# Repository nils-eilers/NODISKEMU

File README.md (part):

NODISKEMU
=========

SD/MMC to IEEE-488 interface/controller
---------------------------------------

Introduction
------------

NODISKEMU is firmware, used in hardware designs like petSD, petSD+ or
Dave Curran's pet microSD that allows the IEEE-488 bus to access
SD cards  - think of it as a CBM 2031 with a modern storage medium instead
of disks. The project was inspired by (and uses a few bits of code from)
MMC2IEC[1] by Lars Pontoppidan and once ran on the same hardware before it
grew too big for the ATmega32 used there.

Currently, the firmware provide good DOS and file-level compatibility with CBM
drives, but much work remains.  Unless specifically noted, anything that tries
to execute code on the device will not work, this includes every software
fastloader.

NODISKEMU is a fork of sd2iec[2] by Ingo Korb (et al.) and is not intended to
be used on devices equipped with a Commodore serial bus, such as MMC2IEC,
SD2IEC or uIEC. Though most code still persists, compilation for these targets
may break at any time or is already broken. You better keep using sd2iec
for those.

1. http://pontoppidan.info/lars/index.php?proj=mmc2iec
2. http://sd2iec.de

Are you kidding me?
-------------------

This actually **IS** a disk emulator, isn't?

NODISKEMU does not emulate any particular vintage Commodore disk drive.
It neither emulates a 6502 CPU nor does it run any Commodore DOS.
It's just a storage solution that is capable to interact on low level
functions such as OPEN or TALK and interprets commands sent to channel 15
in a way similar to other drives.

The deeper meaning of this name is to clarify that there actually are
and ever will be some differences compared to real floppy drives.

Supported cards
---------------
MMC, SD and SHDC cards (resp. microSD/microSDHC cards) are supported,
formatted with either FAT16 or FAT32.

SDXC, microSDXC or ex-FAT won't work.

If you card refuses to work, try to format it with SD Formatter 4.0,
freely available for Windows and Mac from
https://www.sdcard.org/downloads/formatter_4/

Compatibility (IEEE-488)
------------------------

### Known good ###

Devices with IEEE-488 bus are compatible with any CBM/PET computer
equipped with either BASIC 2, BASIC 4 or BSOS.

The CBM-II series are fully supported, however you might want to
upgrade to a recent KERNAL because the older ones contain a couple
of bugs. The PROXA 7000 extension is fully supported.

OS-9 on the SuperPET is reported to boot from the FAT filesystem, but not
from disk images.

### Issues ###

The original PET equipped with BASIC 1 is not compatible because of its
hopelessly broken IEEE routines.

There are known issues with printer interfaces by Ultra Eletronic or
several clones of them, including mine.

### Untested ###

Tests are still missing for the Z-RAM card (a Z80 CP/M board)
and the softbox by Small Systems Engineering, Ltd. which is a Z80 CP/M
computer attached to the IEEE-488 bus.

Directories
-----------

petSD's default unit number became 11 in order to avoid any conflicts
with CBM 8296 built-in drives which usually are set to 8. You may even
use a further disk drive as unit 9 without any conflicts to petSD's 11.

Displaying directories works as usual, either the BASIC 2 way with

```
LOAD"$",11
LIST
```

or `CATALOG` for BASIC 4. You can abbreviate to `cA` and specify the
unit address:

```
cAu11
```

There are however some more advanced features:

### Directory filters ###

To show only directories, both =B (CMD-compatible) and =D can be used.
On a real Commodore drive D matches everything.
To include hidden files in the directory, use *=H - on a 1541 this doesn't
do anything. NODISKEMU marks hidden files with an H after the lock mark,
i.e. "PRG<H" or "PRG H".

CMD-style "short" and "long" directory listings with timestamps are supported
("$=T"), including timestamp filters. Please read a CMD manual for a complete
description of the syntax, two basic examples are provided here:

Short format:
```
LOAD"$=T",11
LIST
```

Long format:
```
LOAD"$=T:*=L",11
LIST
```

### Partition directory ###

The CMD-style partition directory ($=P) is supported, including filters
($=P:S*). All partitions are listed with type "FAT", although this could
change to "NAT" later for compatibility.

### Printing the directory ###

This example assumes a printer attached as unit 4:

```
LOAD "$",11
OPEN 4,4:CMD 4
LIST
PRINT#4:CLOSE 4
```

Sending Disk Commands
---------------------

BASIC 2 has only a very limited number of disk commands built-in:
`LOAD, SAVE, VERIFY, OPEN, CLOSE, GET#, INPUT#` and `PRINT#`.
For anything else beyond basic loading and saving programs and displaying
the directory, you have to send disk commands to the command channel 15
of the drive.

This can be done in two ways, either by appending the command to the OPEN
command or by sending it separately with the PRINT# command. An an example:

```
OPEN1,11,15,"CD:DIRNAME":CLOSE1
```
This opens the logical channel 1 on device 8 and sends the string `CD:DIRNAME`
to the command channel 15.

BASIC 4 adds some more advanced commands such as `CATALOG`. BASIC parses the
given parameters and builds a command string which is then sent to the command
channel 15, so it's just a more convenient wrapper for sending disk commands
but it doesn't add any DOS functions, they're still all processed inside the
disk drive.

However, even though BASIC 4 knows some more disk commands, they're kind of
limited in their usage. The most advanced and most comfortable way is to use a
so called DOS wedge. It cannot be used inside programs, only in direct mode.

Preceed any disk command with a `@` or a `>`, everything after that will be
sent to the command channel 15, e.g.:

```
@CD:DIRNAME
```

A loadable DOS wedge (as a terminate and stay resident program) is available
from http://petsd.net/wedge.php for CBM/PET computers with BASIC 2 and BASIC 4
and from http://cbm2wedge.sourceforge.net for the CBM-II series.

Better yet, get an updated editor ROM with built-in wedge[1] or upgrade your
CBM 8296 to BSOS[2] to have the wedge available right from the start after
power-on.

1. http://www.6502.org/users/sjgray/projects/editrom
2. https://github.com/Edilbert/BSOS

Retrieving the Disk Status
--------------------------

If an error occurs, a red LED of the drive flashes to indicate an error. To
get the error message, you have to retrieve the disk status by reading from
channel 15.

Unfortunately, BASIC 2 has no built-in command for this purpose, so it's
rather cumbersome:

```
10 OPEN1,11,15
20 INPUT#1,E,E$,T,S
30 PRINT E;E$;T;S
40 CLOSE1
```

`INPUT` doesn't work in direct mode, so you'll really have to write a short
program to retrieve and display the disk status.

BASIC 4 does it better, it includes the pseudo variables `ds` and `ds$` which
it updates after disk operations from status channel 15. However, it misses
some changes occasionally so if you depend on really getting the current disk
status you're stuck with the old-fashioned way.

Again, the most comfortable way is to use a DOS wedge. Just hit `@` followed
by RETURN and you'll get always the current disk status.

Long File Names
---------------
Long file names (i.e names not within the 8.3 limits) are supported on
FAT, but for compatibility reasons the 8.3 name is used if the long
name exceeds 16 characters. If you use anything but ASCII characters
on the PC or their PETSCII equivalents on the Commodore you may
get strange characters on the other system because the LFN use
Unicode characters on disk, but NODISKEMU parses only the low byte
of each character in the name.

Valid FAT Filenames
-------------------
Valid characters for filenames on the FAT filesystem have an ASCII code
greater or equal 32 (space) and less or equal 126 ('~'). In general,
no control codes are allowed, only 7 bit ASCII characters minus some
special characters. These forbidden characters are:

        " * , / \ : = ? @

Furthermore, neither space nor the full stop ('.') are not allowed as first
or last character of a filename. If a filename contains any illegal
characters, the creation of X00 files is forced even if XE mode 0 is set.

Changing the Device Address
---------------------------
After power on, the device address gets restored from the EEPROM. If the
device has jumpers or switches to set the address, it will take this
setting if a change is detected compared to the last setting during power-on.

There are up to three ways to change the device address:

1. U0 command (see there)
2. Hardware (jumper or switches)
3. LCD menu system
4. PETSD.CFG, see "Multiple drives" below

Hardware jumpers are only read after power-on, a reset or power
cycle is required to apply any changes.

If there are conflicting situations (e.g. hardware jumpers set to address 10
but address 9 stored in EEPROM), the last change or command sets the address.

EEPROM file system
------------------
**WARNING**: The EEPROM file system is a newly-implemented file system
that may still contain bugs. Do not store data on it that you cannot
afford to lose. Always make sure that you have a backup. Also, the
format may change in later releases, so please expect that the
partition may need to be erased in the future.

Devices running NODISKEMU always have an EEPROM to store the system
configuration, but on some devices this EEPROM is much larger than
required. To utilize the empty space on these devices (currently any
microcontroller with at least 128K of flash), a special EEPROM file
system has been implemented. This can for example be used to store a
small file browser or fast loader so it can be used independent of the
storage medium that is currently inserted.

The EEPROM file system will always register itself on the last
partition number (see "Partitions" below). You can check the list of
partitions ("$=P") to find the current partition number of the EEPROM
file system or use the alias function (see below) to access it.

To simplify calculations, block numbers on the EEPROMFS are calculated
using 256 bytes per block instead of the usual 254 bytes as used by
Commodore drives. Internally, the allocation is even more fine-grained
(using 64 byte sectors), which means that the number of free blocks
shown on an empty file system may be less than the sum of the number
of blocks of all files on a full file system.

The EEPROM file system does not support subdirectories. It can be
formatted using the N: command as usual, but the disk name and ID are
ignored. The capacity of the EEPROM file system varies between
devices: On AVR devices it is 3.25 KBytes and at most 8 files can be
stored on it. On a2iec, the file system can hold 7 KBytes and at most
16 files can be stored on it. The actual number of files that can be
stored depends on the length of the files, longer files need more than
one directory entry.

Partitions
----------

NODISKEMU features a multi-partition support similar to that of the CMD
drives. The partitions (which may be on separate drives for some hardware
configurations) are accessed using the drive number of the commands
sent from the computer and are numbered starting with 1. Partition 0
is a special case: Because most software doesn't support drive numbers
or always sends drive number 0, this partition points to the currently
selected partition. By default, accesses to partition 0 will access
partition 1, this can be changed by sending "CP<num>" over the command
channel with <num> being an ASCII number from 1 to 255. "C<Shift-P"
(0x42 0xd0) works the same, but expects a binary partition number as the
third character of the command.

To allow a "stable" access to the EEPROM file system no matter how
many partitions are currently available, a special character has been
introduced that will always access the EEPROM file system (if
available). When NODISKEMU sees a "!" character where it expects a
partition number and the "!" character is directly followed by a colon
(i.e. "!:"), it will access the EEPROMFS if available. Direct access
using the assigned partition number is of course still
available. Additionally "$!" will always load the directory of the
EEPROM file system partition (if available), similar to "$1" to "$9"
for partitions 1 to 9.

Multiple drives
---------------

With the build option `CONFIG_MULTIDRIVE` (enabled in `config-petSD+`),
a single device can answer on up to 4 bus addresses at the same time.
Each address is either a single drive or a dual drive with drive 0 and
drive 1, like a CBM 4040, 8050 or 8250, so there are up to 8 drives on
one SD card. Each drive points to a directory or to a disk image.

Without a configuration file nothing changes: the device behaves like a
single drive at the address stored in the EEPROM.

### PETSD.CFG ###

The drives are configured in the text file `PETSD.CFG` in the root
directory of the card, one line per drive:

```
# petSD+ drives
8:0  = /
8:1  = /GAMES
9:0  = /WORK
10:0 = /CBM8050/DISK1.D80
10:1 = /CBM8050/DISK2.D80
```

Rules:

- `address:drive = path`, blanks around `:` and `=` are allowed.
- Addresses 4 to 30, drive 0 or 1, at most 4 devices.
- A device needs drive 0, a line for drive 1 makes it a dual drive.
- The path starts at the root directory of the card and names a
  directory or a disk image. Upper and lower case do not matter, the
  maximum length is 112 characters.
- Names longer than 16 characters must be given as 8.3 short name,
  e.g. `/COLLEC~1`.
- Every line that does not match this pattern is a comment, usually
  starting with `#`. A comment after a path is not possible, it would
  become part of the path.
- If a drive is listed twice, the first line counts.
- The file is read at power-on and after every card change.

If the path of drive 1 does not exist, that drive reports
`74,DRIVE NOT READY`. If the path of drive 0 does not exist, the whole
device is missing. If no device is usable, the legacy single drive mode
with the EEPROM address is used.

### Drive numbers ###

With `PETSD.CFG` active, the number in front of the colon is the drive
number of the addressed device, not a partition number:

| Command                 | Meaning                                   |
|-------------------------|-------------------------------------------|
| `$`                     | directory of drive 0, then drive 1        |
| `$1`                    | directory of drive 1                      |
| `NAME` (read)           | search drive 0, then drive 1              |
| `NAME` (write)          | drive 0                                   |
| `0:NAME`, `1:NAME`      | drive 0 or drive 1                        |
| `1:NAME` (single drive) | `74,DRIVE NOT READY`                      |

This matches CBM DOS 2 dual drives, so the BASIC 4 commands work as
expected, e.g. `DIRECTORY D1,U8`, `DLOAD"NAME",D1,U8` or
`COPY D0,"OLD" TO D1,"NEW",U8`. The `C` command copies between drive 0
and drive 1 of the same device. Copying between two different bus
addresses needs the computer in between.

`CD`, `MD` and `RD` take the drive number right after the command:
`CD1:GAMES`, `CD1/GAMES/ACTION/`, `CD1//` (root of the card),
`CD1:_` (left arrow, one level up). Without a number they work on drive 0. Each drive
keeps its own current directory until the next card change or reset,
`PETSD.CFG` is not changed by `CD`.

### Changing addresses ###

- `U0>` and `M-W 119` change the address of the addressed device
  (both drives) until the next card change or reset. An address that is
  already taken or outside 4..30 is rejected with `30,SYNTAX ERROR`.
- `XW` stores the settings in the EEPROM as before. With `PETSD.CFG`
  active, it also writes the new address of the addressed device into
  the file. Only the address field of the lines of that device changes,
  everything else stays as it is. The file is written to `PETSD.TMP`
  first and then renamed.

### LCD menu ###

The main menu entry "Configure drives" replaces "Change device number".
It lists all drives and allows to add and remove devices and drive 1,
to change addresses and to choose a directory or disk image with a file
browser. "Save and exit" writes `PETSD.CFG` line by line, own comments
and blank lines are kept. Without `PETSD.CFG`, changing only the address
stores it in the EEPROM as before and no file is created.

With `PETSD.CFG` active, "Browse files" first asks for the drive to
browse.

### Card change ###

After a card change the configuration of the new card is read. A
command that is still pending for an address which does not exist on
the new card is discarded.

### Limitations ###

- Fast loaders (IEC only) are untested with more than one drive.
- The disk swap list (`XS`, `AUTOSWAP.LST`, swap buttons) is currently
  disabled in the firmware, with or without multiple drives.

x00 files
---------

P00/S00/U00/R00 files are transparently supported, that means they show
up in the directory listing with their internal file name instead of the
FAT file name. Renaming them only changes the internal name. The XE
command defines if x00 extensions are used when writing files, by
default NODISKEMU doesn't create x00 container files.

The creation of x00 files is forced if the filename contains
characters that would be illegal for FAT filenames. Spaces and dots are only
allowed within the filename but not as the first or last character.

Parsing of x00 files is always enabled even when writing them is not.

x00 files are recognized by checking both the extension of the file
(P/S/U/R with a two-digit suffix) and the header signature.

Disk Images
-----------

Disk images are recognized by their file extension (.D64, .D41, .D71, .D81,
.DNP) and their file size (must be one of 174848, 175531, 349696, 351062,
819200 or a multiple of 65536 for DNP). If the image has an error info block
appended it will be used to simulate read errors. Writing to a sector with
an error will always work, but it will not clear the indicated error.
D81 images with error info blocks are not supported.

Warning: There is at least one program out there (DirMaster v2.1/Style by
THE WIZ) which generates broken DNP files. The usual symptom is that
moving from a subdirectory that was created with this program back to
its parent directory using CD:_ (left arrow) sets the current directory
not to the parent directory, but to an incorrect sector instead. A
workaround for this problem in NODISKEMU would require an unreasonable
amount of system resources, so it is recommended to avoid creating
subdirectories with this version of DirMaster. It is possible to fix
this problem using a hex editor, but the exact process is beyond the scope
of this document.

REL files
---------

Partial REL file support is implemented. It should work fine for existing
files, but creating new files and/or adding records to existing files
may fail. REL files in disk images are not supported yet, only as files
on a FAT medium. When x00 support is disabled the first byte of a REL
file is assumed to be the record length.

Large buffers
-------------

To support commands which directly access the storage devices support
for larger buffers was added. A large buffer can be allocated by
opening a file named "##<d>" (exactly three characters" with <d> replaced
by a single digit specifying the number of 256-byte buffers to be
chained into one large buffer - e.g. "##2" for a 512 byte buffer,
"##4" for 1024 bytes etc. Unlike a standard buffer where the read/write
pointer is set to byte 1, a large buffer will start with the r/w pointer
pointing to byte 0 because that seems to be more sensible to the author.

If there aren't enough free buffers to support the size you requested
a 70,NO CHANNEL message is set in the error channel and no file is
opened. If the file name isn't exactly three bytes long a standard
buffer ("#") will be allocated instead for compatibility.

The B-P command supports a third parameter that holds the high byte
of the buffer position, For example, "B-P 9 4 1" positions to byte
260 (1\*256+4) of the buffer on secondary address 9.

LCD file browser
----------------

The LCD file browser uses available sector buffers to cache directory entries.
Even one free buffer is sufficient. If a directory is larger than the cache,
continue with NEXT or PREV to load the adjacent entries automatically.
"Reading..." indicates a reload; this rescans the directory to preserve
directory/image/name sorting on FAT. Disk images retain their native order.
Browser buffers are released before changing directories or mounting images.

Pressing SELECT on a regular file closes the entire menu and returns to the
status screen, on both FAT and inside disk images. Selecting a directory or
disk image enters it as usual. "Return to main menu" still returns to the
main menu.

Holding PREV or NEXT accelerates navigation after two and four seconds,
with repeat intervals of 150, 80 and 40 ms. Releasing the key or changing
direction restarts the initial speed.

Diagnostics
-----------

Because some SD slots seem to suffer from bad/unreliable card detect
switches a test mode for this has been implemented on the units that
have SD card support. To enable this test mode, hold down the PREV
button during power-up.

Devices with built-in LCD support (read: petSD+) will show their
diagnostics on the display if the menu system is enabled (see also:
XM command).

On petSD+, keep PREV held until the startup check has
completed to enter diagnostics, or NEXT to adjust LCD contrast.

The further notes apply only for devices without built-in LCD support
(read: old petSD and pet microSD):

The red (dirty) LED will reflect the card detect status - if the LED
is on the card detect switch is closed. Please note that this does not
indicate successful communication with the card but merely that the
mechanical switch in the SD card slot is closed.

On units with two NODISKEMU-controlled LEDs, the green (busy) LED will
indicate the state of the write protect switch - if the LED is lit,
the write protection is on. Due to the way the write protect notch
works on SD cards, the indication is only valid when the card is fully
inserted into the slot.

To exit from the diagnostic mode, power-cycle the device or push the
NEXT button once.

Other important notes
---------------------

- When you hold down the disk change (forward) button during power
  on the software will use default values instead of those stored
  in the EEPROM. (TODO: currently deactivated)
- File overwrite (@foo) is implemented by deleting the file first.
- File sizes in the directory are in blocks (of 254 bytes), but
  the blocks free message actually reports free clusters. It is
  a compromise of compatibility, accuracy and code size.
- If known, the low byte of the next line link pointer of the directory
  listing will be set to (filesize MOD 254)+2, so you can calculate the
  true size of the file if required. The 2 is added so it can never be
  mistaken for an end marker (0) or for the default value (1, used by at
  least the 1541 and 1571 disk drives).
- If your hardware supports more than one SD card, changing either one
  will reset the current partition to 1 and the current directory of
  all partitions to the root drive. Doing this just for the card that
  was changed would cause lots of problems if the number of partitions
  on the previous and the newly inserted cards are different.
- If you are the author of a program that needs to detect NODISKEMU for
  some reason, DO NOT use M-R for this purpose. Use the UI command
  instead and check the message you get for "nodiskemu" instead.

Reference of Disk Commands
--------------------------

### B-P ##

        B-P: channel position

Set the Buffer-Pointer associated with the given channel to a new value.
`B-P: 2 1` sets channel 2 pointer to the beginning of the data area in the
direct access buffer.

### B-R/B-W ###

        B-R: channel drive track sector
        B-W: channel drive track sector

Reads and writes blocks the clumsy way. Use U1/U2 instead for new programs.

### C ###

File copy command, should be CMD compatible. The syntax is

        C[partition][path]:targetname=[[partition][path]:]sourcename[,[[p][p]:]sourcename...]

You can use this command to copy multiple files into a single target
file in which case all source files will be appended into the target
file. Parsing restarts for every source file name which means that
every source name is assumed to be relative to the current directory.
You can use wildcards in the source names, but only the first
file matching will be copied.

Copying REL files should work, but isn't tested well. Mixing REL and
non-REL files in an append operation isn't supported.

### CD ###

CD (change directory) is used to select the current directory and to
mount or unmount disk images. Subdirectory access is compatible to the
syntax used by the CMD drives, although drive/partition numbers are
completely ignored.

Quick syntax overview:

Command        | Remarks
---------------|------------------------------------------------------------
`CD:_`         |changes into the parent dir (_ is the left arrow on the PET)
`CD_`          |ditto
`CD:foo`       |changes into foo
`CD/foo`       |ditto
`CD//foo`      |changes into \foo
`CD/foo/:bar`  |changes into foo\bar
`CD/foo/bar`   |ditto

You can use wildcards anywhere in the path. To change into an disk
image the image file must be the last component in the path, either
after a slash or a colon character.

To mount/unmount image files, change into them as if they were a directory
and use CD:_ (left arrow on the PET) to leave.
Please note that image files are detected by file extension and file size
and there is no reliable way to see if a file is a valid image file.

### CP, C\<Shift-P> ###

This changes the current partition, see "Partitions" below for details.

### D ###

Direct sector access, this is a command group introduced by NODISKEMU.
Some Commodore drives use D for disk duplication between two drives
in the same unit, an attempt to use that command with NODISKEMU should
result in an error message.

D has three subcommands: DI (Info), DR (Read) and DW (Write).
Each of those commands requires a buffer to be opened (similar
to U1/U2), but due to the larger sector size of the storage devices
used by NODISKEMU it needs to be a large buffer of size 2 (512 bytes)
or larger. The exception is the DI command with page set to 0,
its result will always fit into a standard 256 byte buffer.
If you try to use one of the commands with a buffer that is too
small a new error message is returned, "78,BUFFER TOO SMALL,00,00".

In the following paragraphs the secondary address that was used
to open the buffer is called "bufchan".

### DI ###
In BASIC notation the command format is

        "DI"+chr$(bufchan)+chr$(device)+chr$(page)

`device` is the number of the physical device to be queried,
`page` the information page to be retrieved. Currently the
only page implemented is page 0 which will return the
following data structure:

     1 byte : Number of valid bytes in this structure
              This includes this byte and is meant to provide
              backwards compatibility if this structure is extended
              at a later time. New fields will always be added to
              the end so old programs can still read the fields
              they know about.
     1 byte : Highest diskinfo page supported
              Always 0 for now, will increase if more information
              pages are added (planned: Complete ATA IDENTIFY
              output for IDE and CSD for SD)
     1 byte : Disk type
              This field identifies the device type, currently
              implemented values are:
                0  IDE
                2  SD
                3  (reserved)
     1 byte : Sector size divided by 256
              This field holds the sector size of the storage device
              divided by 256.
     4 bytes: Number of sectors on the device
              A little-endian (same byte order as the 6502) value
              of the number of sectors on the storage device.
              If there is ever a need to increase the reported
              capacity beyond 2TB (for 512 byte sectors) this
              field will return 0 and a 64-bit value will be added
              to this diskinfo page.

If you want to determine if there is a device that responds
to a given number, read info page 0 for it. If there is no
device present that corresponds to the number you will see
a DRIVE NOT READY error on the error channel and the
"number of valid bytes" entry in the structure will be 0.

Do not assume that device numbers are stable between releases
and do not assume that they are continuous either. To scan
for all present devices you should query at least 0-7 for now,
but this limit may increase in later releases.

### DR/DW ###

In BASIC notation the command format would be
```
      "DR"+chr$(bufchan)+chr$(device)
          +chr$(sector AND 255)
          +chr$((sector/256) AND 255)
          +chr$((sector/65536) AND 255)
          +chr$((sector/16777216) AND 255)
```
(or "DW" instead of "DR)

but this won't work on the C64 because AND does not accept
parameters larger than 32767. The principle should be clear
though, the last four bytes are a 32 bit sector number in
little-endian byte order.

DR reads the sector to the buffer, DW writes the contents
of the buffer to the sector. Both commands will update the
error channel if an error occurs, for DR the 20,READ ERROR
was chosen to represent read errors; for write problems
during DW it sets 25,WRITE ERROR for errors and 26,WRITE
PROTECT ON if the device is read-only.

### G-P ###

Get partition info, see CMD FD/HD manual for details. The reported
information is partially faked, feedback is welcome.

### MD ###

Makes (creates) a directory. MD uses a syntax similar to CD and
will create the directory listed after the colon (:) relative to
any directory listed before it.

`MD/foo/:bar` creates bar in foo

`MD//foo/:bar` creates bar in \foo

### M-R, M-W, M-E ###

When no file is set up using XR, M-R will check a small internal
table of common drive-detection addresses and return data that
forces most of the supported fast loaders into a compatible mode
(e.g. 1541 mode for Dreamload and ULoad Model 3, disabled
fastloader for Action Replay 6). If the address is not
recognized, more-or-less random data will be returned.

  Unfortunately GEOS reads rather large parts of the drive ROM
using M-R to detect the drive, which cannot be reasonably added
into the internal table. To enable the GEOS drive detection to
work properly with NODISKEMU and to allow switching between
1541/71/81 modes, file-based M-R emulation has been implemented.
If a file has been set up as M-R data source using the XR
command, its contents will be returned for M-R commands that try
to read an address in the range of $8000-$ffff. The ROM file
should be a copy of the ROM contents of a 1541/71/81 drive (any
headers will be skipped automatically), its name must be 16
characters or less. When an M-R command is received, the file
will be searched in three locations on the storage medium:

1. in the current directory of the current partition
2. in the root directory of the current partition
3. in the root directory of the first partition

The internal emulation table will be used if the file wasn't found
in any of those locations or an error occurred while reading
it. Please be aware that the ROM file is ONLY used for M-R
commands. Except for some very specific situations where drive
detection fails (e.g. GEOS) it will probably decrease compatibility
of NODISKEMU because most of the implemented fast loaders will only
recognize the 1541 variation of the loader.

Memory writing knows about the address used for changing the device
address on a 1541 and will change the address of NODISKEMU to the
requested value. It will also check if the transmitted data
corresponds to any of the known software fastloaders so the correct
emulation code can be used when M-E is called.

### N ###

New (format) a disk image. The corresponding BASIC 4 command is
`HEADER`.

Format works only if a disk image is already mounted. This command will
be ignored for DNP images unless the current directory is the root
directory of the DNP image.

Formatting D80 and D82 disk images is not supported yet.

### P ###

Positioning doesn't just work for REL files but also for regular
files on a FAT partition. When used for regular files the format
is `"P"+chr$(channel)+chr$(lo)+chr$(midlo)+chr$(midhi)+chr$(hi)`
which will seek to the 0-based offset `hi*2^24+midhi*65536+256*midlo+lo`
in the file. If you send less than four bytes for the offset, the
missing bytes are assumed to be zero.

### R ###

Renames a file. Notice that the new name comes first!

        R:NEWNAME=OLDNAME

Renaming files should work the same as it does on CMD drives, although
the errors flagged for invalid characters in the name may differ.

### RD ###

RD (remove directory) can only remove subdirectories of the current directory.

`RD:foo` deletes foo

### S ###

Scratches (deletes) a file.

`S:DELETEME,METOO' deletes `DELETEME` and `METOO`.

Name matching is fully supported, directories are ignored.
Scratching of multiple files separated by , is also supported with no
limit to the number of files except for the maximum command line length
(usually 100 to 120 characters).

### T-R and T-W ###

If your hardware features RTC support the commands T-R (time read) and T-W
(time write) are available. If the RTC isn't present, both commands return
30,SYNTAX ERROR,00,00; if the RTC is present but not set correctly T-R will
return 31,SYNTAX ERROR,00,00.

Both commands expect a fourth character that specifies the time format
to be used. T-W expects that the new time follows that character
with no space or other characters in between. For the A, B and D
formats, the expected input format is exactly the same as returned
by T-R with the same format character; for the I format the day of
week is ignored and calculated based on the date instead.

The possible formats are:

- "A"SCII: "SUN. 01/20/08 01:23:45 PM"+CHR$(13)
  The day-of-week string can be any of "SUN.", "MON.", "TUES", "WED.",
  "THUR", "FRI.", "SAT.". The year field is modulo 100.

- "B"CD or "D"ecimal:
   Both these formats use 9 bytes to specify the time. For BCD everything
   is BCD-encoded, for Decimal the numbers are sent/parsed as-is.

Byte        | Value
------------|----------------------------------------------------------------
           0| Day of the week (0 for Sunday)
           1| Year (modulo 100 for BCD; -1900 for Decimal, i.e. 108 for 2008)
           2| Month (1-based)
           3| Day (1-based)
           4| Hour   (1-12)
           5| Minute (0-59)
           6| Second (0-59)
           7| AM/PM-Flag (0 is AM, everything else is PM)
           8| CHR$(13)

When the time is set a year less than 80 is interpreted as 20xx.
Years after 2099 are not supported. T-W rejects out-of-range years with
31,SYNTAX ERROR,00,00.

- "I"SO 8601 subset: "2008-01-20T13:23:45 SUN"+CHR$(13)
  This format complies with ISO 8601 and adds a day of week
  abbreviation using the same table as the A format, but omitting
  the fourth character. When it is used with T-W, anything beyond
  the seconds field is ignored and the day of week is calculated
  based on the specified date. The year must always be specified
  including the century if this format is used to set the time.
  The supported ISO year range is 1980 through 2099.
  To save space, NODISKEMU only accepts this particular date/time
  representation when setting the time with T-WI and no other ISO
  8601-compliant representation.

### U0 ###

  Device address changing with "U0>"+chr$(new address) is supported,
  other U0 commands are currently not implemented.

### U1/U2 ###

Block reading and writing is fully supported while a disk image is mounted.

`U1 channel drive track sector` reads a block,
`U2 channel drive track sector` writes a block

### UI/UJ ###

Soft/Hard reset - UI just sets the "73,..." message on the error channel,
UJ closes all active buffers but doesn't reset the current directory,
mounted image, swap list or anything else.

### U < Shift-J > ###

Real hard reset - this command causes a restart of the AVR processor
(skipping the bootloader if installed). < Shift-J > is character code 202.

X: Extended commands
--------------------

### XEnum ###

Sets the "file extension mode". This setting controls if
files on FAT are written with an x00 header and extension or not.
Possible values for num are:

        0: Never write x00 format files.
        1: Write x00 format files for SEQ/USR/REL, but not for PRG
        2: Always write x00 format files.
        3: Use SEQ/USR/REL file extensions, no x00 header
        4: Same as 3, but also for PRG

If you set mode 3 or 4, extension hiding is automatically enabled.
This setting can be saved in the EEPROM using XW, the default
value is 0.

For compatibility with existing programs that write D64 files,
PRG files that have D64, D41, D71, D81, D80, D82 or DNP as an extension
will always be written without an x00 header and without
any additional PRG file extension.

### XE+ / XE- ###
Enable/disable extension hiding. If enabled, files in FAT with
a PRG/SEQ/USR/REL extension will have their extension removed
and the file type changed to the type specified by the file
extension - e.g. APPLICATION.PRG will become a PRG file named
"APPLICATION", "README.SEQ" will become a SEQ file named "README".
This flag can be saved in the EEPROM using XW, the default
value is disabled (-).

### XInum ###
Switches the display mode for disk images.
num can be 0, in which case the file will be shown
with its normal type in the directory or 1 which will show all
mountable files as DIRectory entries (but they can still be
accessed as files too) or 2 in which case they will show up
twice - once with its normal type and once as directory.
The default value is 0 and this setting can be stored
permanently using XW.

It may be useful to set it to 1 or 2 when using software that
was originally written for CMD devices and which wouldn't
recognize disk images files as mountable on its own.
However, due to limitations of the current implementation of
the CD command such software may still fail to mount a disk
image with this option enabled.

### X\*+ / X\*-  ###
Enable/disable 1581-style * matching. If enabled, characters
after a * will be matched against the end of the file name.
If disabled, any characters after a * will be ignored.
This flag can be saved in the EEPROM using XW, the default value
is enabled (+).

###XDdrv=val ###
Configure drives.  On ATA-based units or units with multiple
drive types, this command can be used to enable or reorder
the drives.  drv is the drive slot (0-7), while val is one
of:

                0: Master ATA device
                1: Slave ATA device
                4: Primary SD/MMC device
                5: Secondary SD/MMC device
                6: (reserved)
               15: no device

Note that only devices supported by the specific hardware
can be selected.  Unsupported device types will return an
error if requested.  Also, note that you cannot select a device
in multiple drive slots.  Finally, while it is possible to
re-order ATA devices using this functionality, it is strongly
discouraged.  Use the master/slave jumpers on the ATA devices
instead.  To reset the drive configuration, set all drive slots
to "no device".  This value can be permanently saved in the
EEPROM using XW.

### XD? ###

View the current drive configuration.  Example result:
`03,D:00=04:01=00:02=01,10,01`  The track indicates the
current device address, while the sector indicates extended
drive configuration status information.

### XM+ / XM- ###
Enable/disable the LCD menu system, only available on some devices. If
disabled, signal lines used for buttons may get used to read the device
address from DIP switches. This command automatically saves the settings
into the EEPROM and restarts the device to apply them. The default value
is enabled (+).

### X ###
X without any following characters reports the current state
of all extended parameters via the error channel, similar
to DolphinDOS. Example result: "03,J-:C152:E01+:B+:*+,08,00"
The track indicates the current device address.

### XS:name ###

Set up a swap list. Lines starting with a semicolon (`;`) are comments
and are skipped when parsing the list.

### XS ###
Disable swap list

### XR:name ###
Set the file used for file-based M-R emulation.

### XR ###
Disable file-based M-R emulation.

See "M-R, M-W, M-E" below. This setting can be
 permanently saved in the EEPROM using XW.

### XW ###

Store configuration to EEPROM

This commands stores the current configuration in the EEPROM.
It will automatically be read when the AVR is reset, so
any changes you made will persist even after turning off
the hardware.

The stored configuration include the extension mode,
drive configuration and the current device address.
If you have changed the device address by software,
NODISKEMU will power up with that address unless
you have changed the device address jumpers (if available) to
a different setting than the one active at the time the
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
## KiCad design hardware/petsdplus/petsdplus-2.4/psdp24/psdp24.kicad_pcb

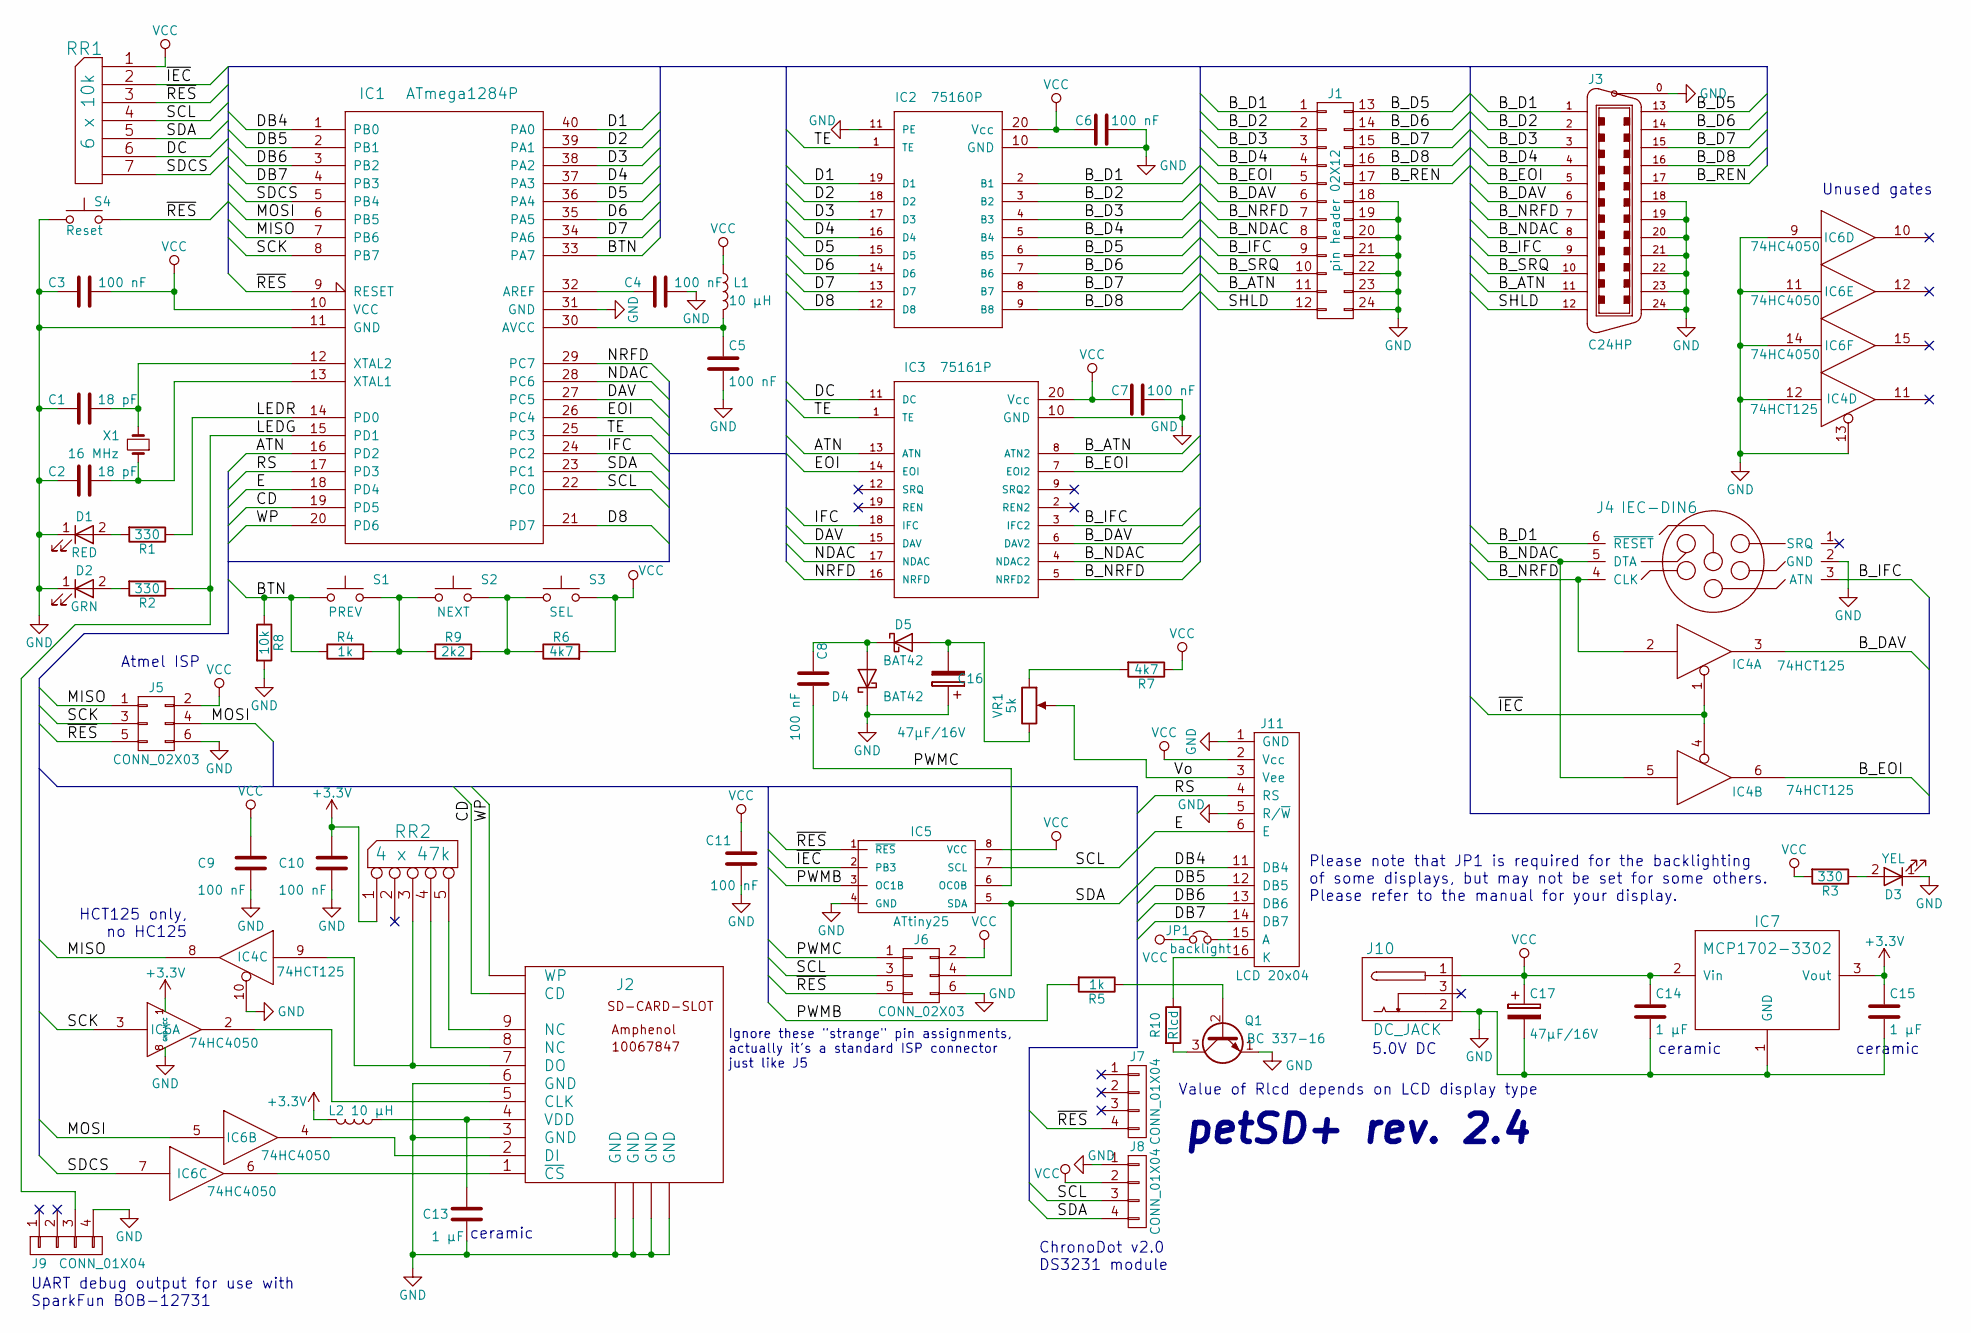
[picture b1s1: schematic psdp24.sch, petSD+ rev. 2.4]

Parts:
C1, C2: 18 pF; C_Disc_D3.8mm_W2.6mm_P2.50mm
C3, C4, C5, C6, C7, C8, C9, C10, C11: 100 nF; C_Disc_D5.0mm_W2.5mm_P5.00mm
C13, C14, C15: 1 µF; C_Disc_D5.0mm_W2.5mm_P5.00mm
C16, C17: 47µF/16V; CP_Axial_L11.0mm_D6.0mm_P18.00mm_Horizontal
D1: RED; LED_D3.0mm
D2: GRN; LED_D3.0mm
D3: YEL; LED_D3.0mm
D4, D5: BAT42; D_DO-35_SOD27_P7.62mm_Horizontal
IC1: ATmega1284P; DIP-40_W15.24mm
IC2: 75160P; DIP-20_W7.62mm
IC3: 75161P; DIP-20_W7.62mm
IC4: 74HCT125; DIP-14_W7.62mm
IC5: ATtiny25; DIP-8_W7.62mm
IC6: 74HC4050; DIP-16_W7.62mm
IC7: MCP1702-3302; TO-92
J1: pin header 02X12; WSL-IEEE488-12-13
J2: SD slot 10067847; SD-SOCKET
J3: C24HP; con-amp-champ-24HP
J4: IEC-DIN6; MAB6H
J5, J6: CONN_02X03; WSL_6W
J7, J8, J9: CONN_01X04; Pin_Header_Straight_1x04_Pitch2.54mm
J10: DC_JACK; BARREL_JACK
J11: LCD 20x04; LCD2004
JP1: backlight; Pin_Header_Straight_1x02_Pitch2.54mm
L1, L2: 10 µH; L_Axial_L7.0mm_D3.3mm_P10.16mm_Horizontal_Fastron_MICC
Q1: BC 337-16; TO-92
R1, R2, R3: 330; R_Axial_DIN0207_L6.3mm_D2.5mm_P10.16mm_Horizontal
R4, R5: 1k; R_Axial_DIN0207_L6.3mm_D2.5mm_P10.16mm_Horizontal
R6, R7: 4k7; R_Axial_DIN0207_L6.3mm_D2.5mm_P10.16mm_Horizontal
R8: 10k; R_Axial_DIN0207_L6.3mm_D2.5mm_P10.16mm_Horizontal
R9: 2k2; R_Axial_DIN0207_L6.3mm_D2.5mm_P10.16mm_Horizontal
R10: Rlcd; R_Axial_DIN0207_L6.3mm_D2.5mm_P10.16mm_Horizontal
RR1: 6 x 10k; R_Array_SIP7
RR2: 4 x 47k; R_Array_SIP5
S1: PREV; PHAP3301
S2: NEXT; PHAP3301
S3: SEL; PHAP3301
S4: Reset; TASTER_3305
VR1: 5k; Potentiometer_Trimmer_Piher_PT-6v_Horizontal_MountLS
X1: 16 MHz; Crystal_HC49-4H_Vertical

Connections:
+3V3: C10.1, C15.1, IC6.1 (VCC), IC7.3 (Vout), L2.2, RR2.1 (COM)
/ATN: IC1.16 (PD2), IC3.13 (ATN)
/BTN: IC1.33 (PA7), R4.1, R8.1, S1.2
/B_ATN: IC3.8 (ATN2), J1.11, J3.11
/B_D1: IC2.2 (B1), J1.1, J3.1, J4.6 (~RESET)
/B_D2: IC2.3 (B2), J1.2, J3.2
/B_D3: IC2.4 (B3), J1.3, J3.3
/B_D4: IC2.5 (B4), J1.4, J3.4
/B_D5: IC2.6 (B5), J1.13, J3.13
/B_D6: IC2.7 (B6), J1.14, J3.14
/B_D7: IC2.8 (B7), J1.15, J3.15
/B_D8: IC2.9 (B8), J1.16, J3.16
/B_DAV: IC3.6 (DAV2), IC4.3, J1.6, J3.6
/B_EOI: IC3.7 (EOI2), IC4.6, J1.5, J3.5
/B_IFC: IC3.3 (IFC2), J1.9, J3.9, J4.3 (ATN)
/B_NDAC: IC3.4 (NDAC2), IC4.5, J1.8, J3.8, J4.5 (DTA)
/B_NRFD: IC3.5 (NRFD2), IC4.2, J1.7, J3.7, J4.4 (CLK)
/B_REN: J1.17, J3.17
/B_SRQ: J1.10, J3.10
/CD: IC1.19 (PD5), J2.CD
/D1: IC1.40 (PA0), IC2.19 (D1)
/D2: IC1.39 (PA1), IC2.18 (D2)
/D3: IC1.38 (PA2), IC2.17 (D3)
/D4: IC1.37 (PA3), IC2.16 (D4)
/D5: IC1.36 (PA4), IC2.15 (D5)
/D6: IC1.35 (PA5), IC2.14 (D6)
/D7: IC1.34 (PA6), IC2.13 (D7)
/D8: IC1.21 (PD7), IC2.12 (D8)
/DAV: IC1.27 (PC5), IC3.15 (DAV)
/DB4: IC1.1 (PB0), J11.11 (DB4)
/DB5: IC1.2 (PB1), J11.12 (DB5)
/DB6: IC1.3 (PB2), J11.13 (DB6)
/DB7: IC1.4 (PB3), J11.14 (DB7)
/DC: IC3.11 (DC), RR1.6
/E: IC1.18 (PD4), J11.6 (E)
/EOI: IC1.26 (PC4), IC3.14 (EOI)
/IFC: IC1.24 (PC2), IC3.18 (IFC)
/LEDG: IC1.15 (PD1), J9.3, R2.1
/LEDR: IC1.14 (PD0), R1.1
/MISO: IC1.7 (PB6), IC4.8, J5.1
/MOSI: IC1.6 (PB5), IC6.5, J5.4
/NDAC: IC1.28 (PC6), IC3.17 (NDAC)
/NRFD: IC1.29 (PC7), IC3.16 (NRFD)
/PWMB: IC5.3 (OC1B), R5.2
/PWMC: C8.2, IC5.6 (OC0B), J6.1
/RS: IC1.17 (PD3), J11.4 (RS)
/SCK: IC1.8 (PB7), IC6.3, J5.3
/SCL: IC1.22 (PC0), IC5.7 (SCL), J6.3, J8.3, RR1.4
/SDA: IC1.23 (PC1), IC5.5 (SDA), J6.4, J8.4, RR1.5
/SDCS: IC1.5 (PB4), IC6.7, RR1.7
/SHLD: J1.12, J3.12
/TE: IC1.25 (PC3), IC2.1 (TE), IC3.1 (TE)
/Vo: J11.3 (Vee), VR1.2
/WP: IC1.20 (PD6), J2.WP
/~IEC: IC4.1, IC4.4, IC5.2 (PB3), RR1.2
/~RES: IC1.9 (RESET), IC5.1 (~RES), J5.5, J6.5, J7.4, RR1.3, S4.2
GND: C1.1, C2.1, C3.1, C4.2, C5.2, C6.1, C7.1, C9.2, C10.2, C11.1, C13.2, C14.2, C15.2, C16.1, C17.2, D1.1 (K), D2.1 (K), D3.1 (K), D4.1 (K), IC1.11 (GND), IC1.31 (GND), IC2.10 (GND), IC2.11 (PE), IC3.10 (GND), IC4.7 (GND), IC4.10, IC4.12, IC4.13, IC5.4 (GND), IC6.8 (GND), IC6.9, IC6.11, IC6.14, IC7.1 (GND), J1.18, J1.19, J1.20, J1.21, J1.22, J1.23, J1.24, J1.25, J1.26, J2.3 (GND), J2.6 (GND), J2.GND1 (GND), J2.GND2 (GND), J2.GND3 (GND), J2.GND4 (GND), J3.0, J3.18, J3.19, J3.20, J3.21, J3.22, J3.23, J3.24, J4.2 (GND), J5.6, J6.6, J8.1, J9.4, J10.2, J11.1 (GND), J11.5 (R/~W), Q1.1 (E), R8.2, S4.1, VR1.0
unnamed: C1.2, IC1.12 (XTAL2), X1.2
unnamed: C2.2, IC1.13 (XTAL1), X1.1
unnamed: C4.1, IC1.32 (AREF)
unnamed: C5.1, IC1.30 (AVCC), L1.2
unnamed: C8.1, D4.2 (A), D5.1 (K)
unnamed: C13.1, J2.4 (VDD), L2.1
unnamed: C16.2, D5.2 (A), VR1.3
unnamed: D1.2 (A), R1.2
unnamed: D2.2 (A), R2.2
unnamed: D3.2 (A), R3.1
unnamed: IC4.9, J2.7 (DO), RR2.3
unnamed: IC6.2, J2.5 (CLK)
unnamed: IC6.4, J2.2 (DI)
unnamed: IC6.6, J2.1 (~CS)
unnamed: J2.8 (NC), RR2.4
unnamed: J2.9 (NC), RR2.5
unnamed: J11.15 (A), JP1.2
unnamed: J11.16 (K), R10.1
unnamed: Q1.2 (B), R5.1
unnamed: Q1.3 (C), R10.2
unnamed: R4.2, R9.1, S1.1, S2.2
unnamed: R6.1, R9.2, S2.1, S3.2
unnamed: R7.2, VR1.1
VCC: C3.2, C6.2, C7.2, C9.1, C11.2, C14.1, C17.1, IC1.10 (VCC), IC2.20 (Vcc), IC3.20 (Vcc), IC4.14 (VCC), IC5.8 (VCC), IC7.2 (Vin), J5.2, J6.2, J8.2, J10.1, J11.2 (Vcc), JP1.1, L1.1, R3.2, R6.2, R7.1, RR1.1 (COM), S3.1

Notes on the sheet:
ceramic
5.0V DC
petSD+ rev. 2.4
ChronoDot v2.0 DS3231 module
Unused gates
HCT125 only, no HC125
Value of Rlcd depends on LCD display type
Ignore these "strange" pin assignments, actually it's a standard ISP connector just like J5
Atmel ISP
UART debug output for use with SparkFun BOB-12731
Please note that JP1 is required for the backlighting of some displays, but may not be set for some others. Please refer to the manual for your display.

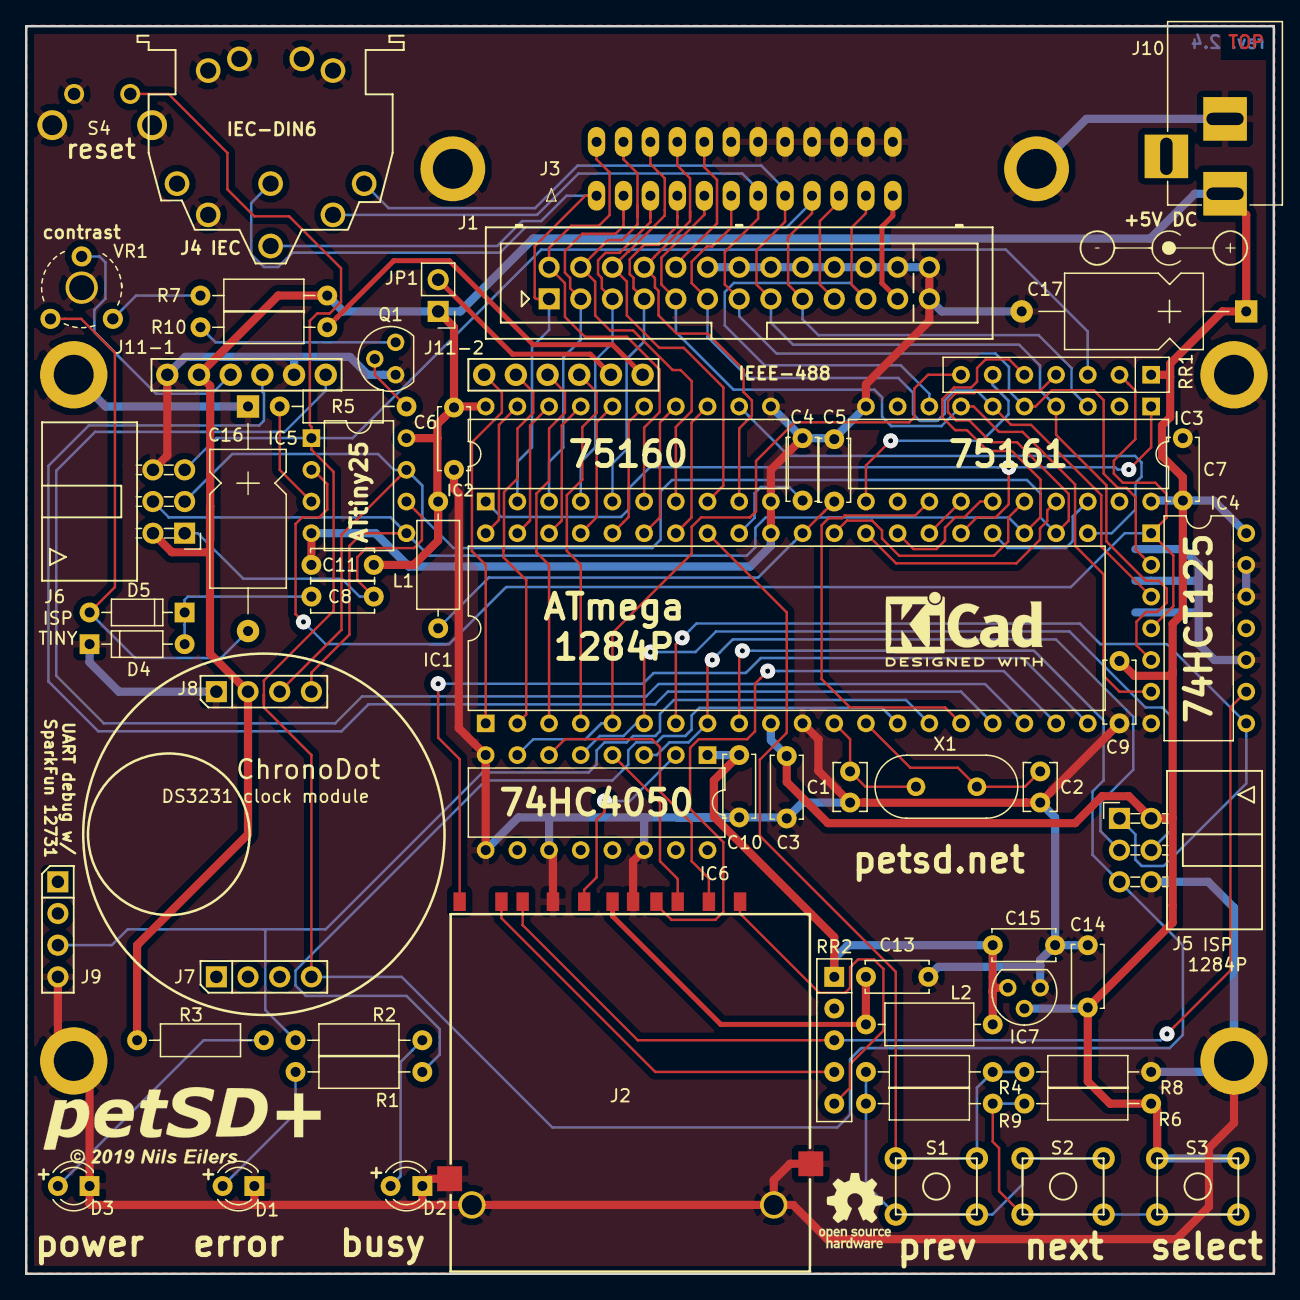
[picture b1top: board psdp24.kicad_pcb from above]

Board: 2 copper layers, 100.0 x 100.0 mm, 61 parts (0 on the bottom side), 81 nets.

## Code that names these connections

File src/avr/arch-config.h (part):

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
#include <avr/io.h>
#include <avr/interrupt.h>
/* Include avrcompat.h to get the PA0..PD7 macros on 1284P */
#include "avrcompat.h"

/* ----- Common definitions for all AVR hardware variants ------ */
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/* Initialize all pins and interrupts related to SD - except SPI */
static inline void sdcard_interface_init(void) {
  /* card detect (SD1) */
  DDRD  &= ~_BV(PD2);
  PORTD |=  _BV(PD2);
  /* write protect (SD1) */
  DDRD &= ~_BV(PD6);
  PORTD |= _BV(PD6);
  /* card change interrupt (SD1) */
  EICRA |= _BV(ISC00);
  EIMSK |= _BV(INT0);
  // Note: Wrapping SD2 in CONFIG_TWINSD may be a good idea
  /* chip select (SD2) */
  PORTD |= _BV(PD4);
  DDRD |= _BV(PD4);
  /* card detect (SD2) */
  DDRD &= ~_BV(PD3);
  PORTD |= _BV(PD3);
  /* write protect (SD2) */
  DDRD &= ~_BV(PD7);
  PORTD |= _BV(PD7);
  /* card change interrupt (SD2) */
  EICRA |=  _BV(ISC90); // Change interrupt
  EIMSK |=  _BV(INT9);  // Change interrupt
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/* sdcard_detect() must return non-zero while a card is inserted */
/* This must be a pin capable of generating interrupts.          */
static inline uint8_t sdcard_detect(void) {
  return !(PIND & _BV(PD2));
}

/* Returns non-zero when the currently inserted card is write-protected */
static inline uint8_t sdcard_wp(void) {
  return PIND & _BV(PD6);
}

/* Support for a second SD card - use CONFIG_TWINSD=y in your config file to enable! */
/* Same as the two functions above, but for card 2 */
static inline uint8_t sdcard2_detect(void) {
  return !(PIND & _BV(PD3));
}
static inline uint8_t sdcard2_wp(void) {
  return PIND & _BV(PD7);
}

/* SD card 1 is assumed to use the standard SS pin   */
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/* SD card 2 CS pin */
static inline __attribute__((always_inline)) void sdcard2_set_ss(uint8_t state) {
  if (state)
    PORTD |= _BV(PD4);
  else
    PORTD &= ~_BV(PD4);
}

/* SD Card supply voltage - choose the one appropiate to your board */
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/*** Device address selection ***/
/* device_hw_address() returns the hardware-selected device address */
static inline uint8_t device_hw_address(void) {
  return 8 + !(PIND & _BV(PD7)) + 2*!(PIND & _BV(PD5));
}

/* Configure hardware device address pins */
static inline void device_hw_address_init(void) {
  DDRD  &= ~(_BV(PD7) | _BV(PD5));
  PORTD |=   _BV(PD7) | _BV(PD5);
}


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static inline void leds_init(void) {
  /* Note: Depending on the chip and register these lines can compile */
  /*       to one instruction each on AVR. For two bits this is one   */
  /*       instruction shorter than "DDRC |= _BV(PC0) | _BV(PC1);"    */
  DDRC |= _BV(PC0);
  DDRC |= _BV(PC1);
}

/* --- "BUSY" led, recommended color: green (usage similiar to 1541 LED) --- */
static inline __attribute__((always_inline)) void set_busy_led(uint8_t state) {
  if (state)
    PORTC |= _BV(PC0);
  else
    PORTC &= ~_BV(PC0);
}

/* --- "DIRTY" led, recommended color: red (errors, unwritten data in memory) --- */
#  define LED_DIRTY_PORT        PORTC
#  define LED_DIRTY_INPUT       PINC
#  define LED_DIRTY_PIN         PC1


/*** IEC signals ***/
#  define IEC_INPUT PINA
#  define IEC_DDR   DDRA
#  define IEC_PORT  PORTA

/* Pins assigned for the IEC lines */
#  define IEC_PIN_ATN   PA0
#  define IEC_PIN_DATA  PA1
#  define IEC_PIN_CLOCK PA2
#  define IEC_PIN_SRQ   PA3

/* Use separate input/output lines?                                    */
/* The code assumes that the input is NOT inverted, but the output is. */
//#  define IEC_SEPARATE_OUT
//#  define IEC_OPIN_ATN   PA4
//#  define IEC_OPIN_DATA  PA5
//#  define IEC_OPIN_CLOCK PA6
//#  define IEC_OPIN_SRQ   PA7

/* You can use different ports for input and output bits. The code tries */
/* to not stomp on the unused bits. IEC output is on IEC_PORT.           */
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
/*** User interface ***/
/* Button NEXT changes to the next disk image and enables sleep mode (held) */
#  define BUTTON_NEXT _BV(PC4)

/* Button PREV changes to the previous disk image */
#  define BUTTON_PREV _BV(PC3)

/* Read the raw button state - a depressed button should read as 0 */
static inline rawbutton_t buttons_read(void) {
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#  define SOFTI2C_PORT    PORTC
#  define SOFTI2C_PIN     PINC
#  define SOFTI2C_DDR     DDRC
#  define SOFTI2C_BIT_SCL PC4
#  define SOFTI2C_BIT_SDA PC5
#  define SOFTI2C_DELAY   6


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#  define SPI_DIVISOR_FAST 4

static inline void sdcard_interface_init(void) {
  DDRD &= ~_BV(PD2);
  PORTD |= _BV(PD2);
  DDRD &= ~_BV(PD6);
  PORTD |= _BV(PD6);
  EICRA |= _BV(ISC00);
  EIMSK |= _BV(INT0);
}

static inline uint8_t sdcard_detect(void) {
  return !(PIND & _BV(PD2));
}

static inline uint8_t sdcard_wp(void) {
  return PIND & _BV(PD6);
}

static inline uint8_t device_hw_address(void) {
  return 8 + !(PIND & _BV(PD7)) + 2*!(PIND & _BV(PD5));
}

static inline void device_hw_address_init(void) {
  DDRD  &= ~(_BV(PD7)|_BV(PD5));
  PORTD |=   _BV(PD7)|_BV(PD5);
}

static inline void leds_init(void) {
  DDRC |= _BV(PC0);
  DDRC |= _BV(PC1);
}

static inline __attribute__((always_inline)) void set_busy_led(uint8_t state) {
  if (state)
    PORTC |= _BV(PC0);
  else
    PORTC &= ~_BV(PC0);
}

#  define LED_DIRTY_PORT        PORTC
#  define LED_DIRTY_INPUT       PINC
#  define LED_DIRTY_PIN         PC1


#  define IEC_INPUT             PINA
#  define IEC_DDR               DDRA
#  define IEC_PORT              PORTA
#  define IEC_PIN_ATN           PA0
#  define IEC_PIN_DATA          PA1
#  define IEC_PIN_CLOCK         PA2
#  define IEC_PIN_SRQ           PA3
#  define IEC_ATN_INT_VECT      PCINT0_vect
#  define IEC_PCMSK             PCMSK0

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  PCIFR |= _BV(PCIF0);
}

#  define BUTTON_NEXT           _BV(PC4)
#  define BUTTON_PREV           _BV(PC3)

static inline rawbutton_t buttons_read(void) {
  return PINC & (BUTTON_NEXT | BUTTON_PREV);
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#  define SPI_DIVISOR_FAST 4

static inline void sdcard_interface_init(void) {
  DDRD  &= ~_BV(PD2);
  PORTD |=  _BV(PD2);
  DDRD  &= ~_BV(PD6);
  PORTD |=  _BV(PD6);
  EICRA |=  _BV(ISC00);
  EIMSK |=  _BV(INT0);
}

static inline uint8_t sdcard_detect(void) {
  return !(PIND & _BV(PD2));
}

static inline uint8_t sdcard_wp(void) {
  return PIND & _BV(PD6);
}

static inline uint8_t device_hw_address(void) {
  return 8 + !(PINA & _BV(PA2)) + 2*!(PINA & _BV(PA3));
}

static inline void device_hw_address_init(void) {
  DDRA  &= ~(_BV(PA2)|_BV(PA3));
  PORTA |=   _BV(PA2)|_BV(PA3);
}

static inline void leds_init(void) {
  DDRA |= _BV(PA0);
  DDRA |= _BV(PA1);
}

static inline __attribute__((always_inline)) void set_busy_led(uint8_t state) {
  if (state)
    PORTA &= ~_BV(PA0);
  else
    PORTA |= _BV(PA0);
}

#  define LED_DIRTY_PORT        PORTA
#  define LED_DIRTY_INPUT       PINA
#  define LED_DIRTY_PIN         PA1


#  define IEC_INPUT             PINC
#  define IEC_DDR               DDRC
#  define IEC_PORT              PORTC
#  define IEC_PIN_ATN           PC0
#  define IEC_PIN_DATA          PC1
#  define IEC_PIN_CLOCK         PC2
#  define IEC_PIN_SRQ           PC3
#  define IEC_ATN_INT_VECT      PCINT2_vect
#  define IEC_PCMSK             PCMSK2

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  PCIFR |= _BV(PCIF2);
}

#  define BUTTON_NEXT           _BV(PA5)
#  define BUTTON_SELECT         _BV(PA4)

static inline void buttons_init(void) {
  DDRA  &= (uint8_t)~(BUTTON_NEXT | BUTTON_SELECT);
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#  define SOFTI2C_PORT          PORTC
#  define SOFTI2C_PIN           PINC
#  define SOFTI2C_DDR           DDRC
#  define SOFTI2C_BIT_SCL       PC6
#  define SOFTI2C_BIT_SDA       PC5
#  define SOFTI2C_BIT_INTRQ     PC7
#  define SOFTI2C_DELAY         6


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}

static inline void sdcard_interface_init(void) {
  DDRB   &= ~_BV(PB7);
  PORTB  |=  _BV(PB7);
  DDRB   &= ~_BV(PB6);
  PORTB  |=  _BV(PB6);
  PCMSK0 |=  _BV(PCINT7);
  PCICR  |=  _BV(PCIE0);
  PCIFR  |=  _BV(PCIF0);
}

static inline uint8_t sdcard_detect(void) {
  return !(PINB & _BV(PB7));
}

static inline uint8_t sdcard_wp(void) {
  return PINB & _BV(PB6);
}

static inline uint8_t device_hw_address(void) {
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
#  define IEC_INPUT             PINE
#  define IEC_DDR               DDRE
#  define IEC_PORT              PORTE
#  define IEC_PIN_ATN           PE6
#  define IEC_PIN_DATA          PE4
#  define IEC_PIN_CLOCK         PE5
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#  define SOFTI2C_PORT          PORTD
#  define SOFTI2C_PIN           PIND
#  define SOFTI2C_DDR           DDRD
#  define SOFTI2C_BIT_SCL       PD0
#  define SOFTI2C_BIT_SDA       PD1
#  define SOFTI2C_BIT_INTRQ     PD2
#  define SOFTI2C_DELAY         6

/* parallel cable - conflicts with the SOFTI2C pins above! */
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#    define PARALLEL_HPORT        PORTB
#    define PARALLEL_HPIN         PINB
#    define PARALLEL_HSK_OUT_BIT  5         // CONN2 pin 14, to C64 FLAG2
#    define PARALLEL_HSK_IN_BIT   4         // CONN2 pin 16, to C64 PC2
#    define PARALLEL_PCMSK        PCMSK0
#    define PARALLEL_PCINT_GROUP  0
#  elif defined(CONFIG_PARALLEL_DOLPHIN)
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#  define SPI_DIVISOR_FAST 4

static inline void sdcard_interface_init(void) {
  DDRD  &= ~_BV(PD2);
  PORTD |=  _BV(PD2);
  DDRD  &= ~_BV(PD6);
  PORTD |=  _BV(PD6);
  EICRA |=  _BV(ISC00);
  EIMSK |=  _BV(INT0);
#ifdef CONFIG_TWINSD
  PORTD |=  _BV(PD3); // CS
  DDRD  |=  _BV(PD3); // CS
  DDRC  &= ~_BV(PC7); // WP
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

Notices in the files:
src/avr/arch-config.h:
Copyright (C) 2007-2026  Ingo Korb <ingo@akana.de>
Copyright (C) 2015-2018  Nils Eilers <nils.eilers@gmx.de>
This program is free software; you can redistribute it and/or modify
it under the terms of the GNU General Public License as published by
the Free Software Foundation; version 2 of the License only.
README.md:
Copyright:
Copyright (C) 2007-2026  Ingo Korb
Copyright (C) 2015-2026 Nils Eilers
NODISKEMU is a fork of sd2iec by Ingo Korb (et al.), http://sd2iec.de
Parts based on code from others, see comments in main.c for details.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
